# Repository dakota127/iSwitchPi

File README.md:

# iSwitchPi
Intelligent Power Switch for Raspberry Pi 

Native Raspberry Pi does not have an On/Off switch and there is no easy way
to shutdown the Pi while keeping the filesystem intact.
This Intelligent Power Switch allows just that: 
Power-On the Pi by pressing a pushbutton and also properly Power-Off
the Pi with another press on the same button.
The intelligence is provided by a program running in an AVR MCU ATtiny44.
This C-program implements a Finite State Machine in the MCU.
A small Python script is running in the Pi itself. 
Just one GPIO-Pin is used for two-way communication.
In addition, a variable frequency square wave is available for externally interrupting the Pi.

Formfactor: Raspi hat with 2x20 Pins for other hats on top of iSwitchPi.

Full Documentation, Code and EagleCAD files on GitHub. 
Documentation is in English and German.
Quick Start guide explains installation.  
See state diagram to understand operation of iSwitchPi

Also check out my project webpage at 
http://projects.descan.com/projekt5.html

Update April 2017:
In April of 2017 an update was made to the firmware in the ATtiny44. 
A user requested an auto-power-on functionality: the Pi should restart 
unattended (meaning without the need to press the ON-pushbutton) when 5 Volt comes back after a power failure. 
State 0 was added to the state diagram  and position 4 of dip-switch 3 is used to select/deselect this feature.

Free to use, modify, and distribute with proper attribution.
Frei für jedermann, vollständige Quellangabe vorausgesetzt.

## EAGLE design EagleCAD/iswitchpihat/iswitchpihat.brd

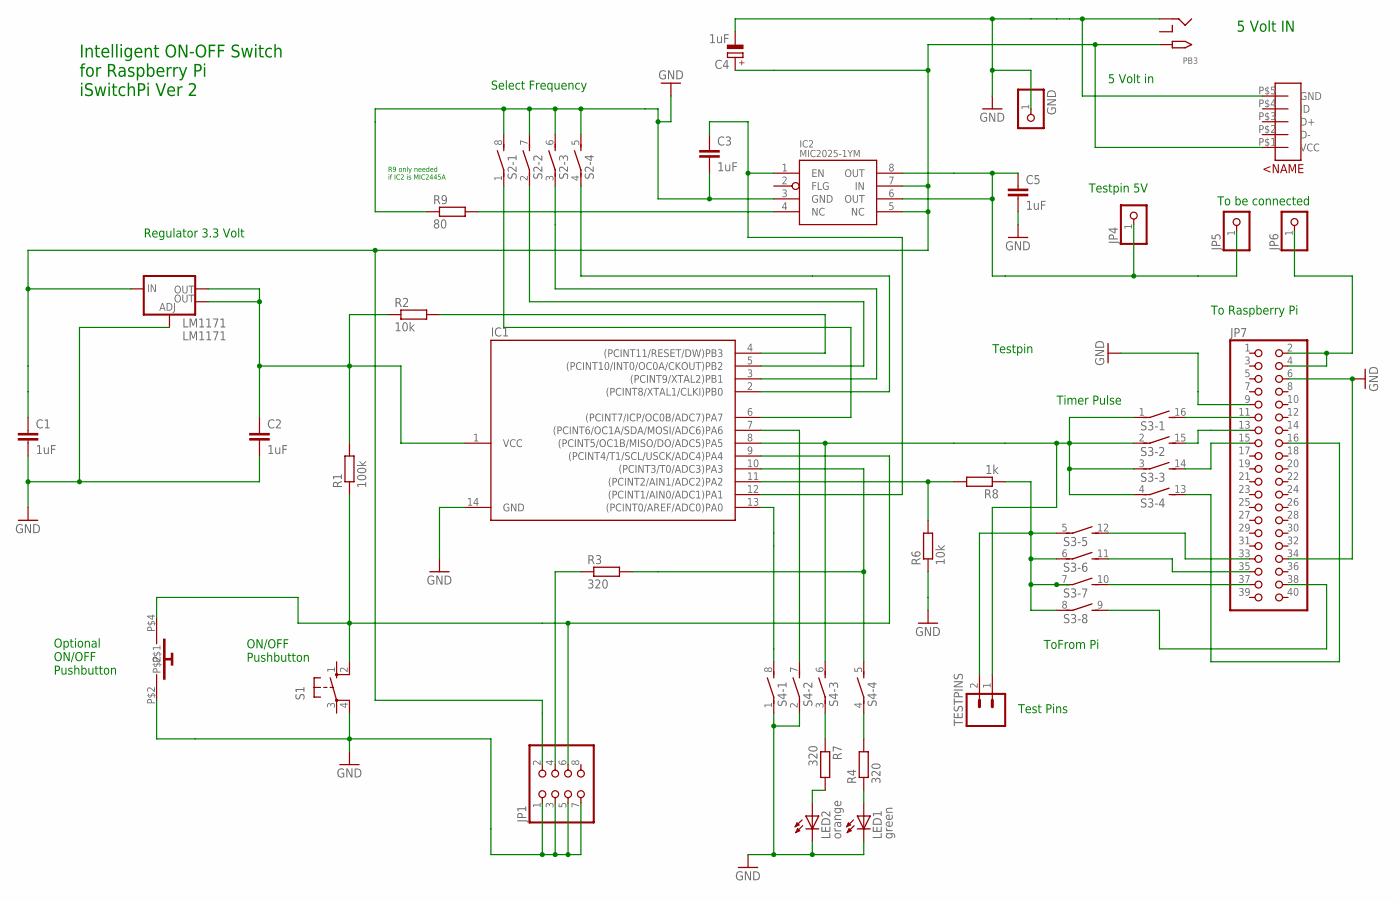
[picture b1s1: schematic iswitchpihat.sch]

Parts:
C1, C2, C3, C5: 1uF; C1206
C4: 1uF; E2,5-6E
GND: PINHD-1X1; 1X01
IC1: ATTINY24/44/84-PU; DIL14
IC2: MIC2025-1YM; SO08
JP1: PINHD-2X4; 2X04
JP4, JP5, JP6: PINHD-1X1; 1X01
JP7: PINHD-2X20-BIG; 2X20-BIG
LED1: green; 1206
LED2: orange; 1206
LM1171: LM1171; SOT223
PB1: PB6A-ELEDIS; PA52
PB3: 2.1MMJACK; ISWITCHPI_PJ-SMALLHOLES
PB4: USBMICRO; ADAUSBMICRO
R1: 100k; 0204/7
R2, R6: 10k; 0204/7
R3, R4, R7: 320; 0204/7
R8: 1k; 0204/7
R9: 80; 0204/7
S1: 10-XX; B3F-10XX
S2, S4: DIP04S
S3: DIP08S
TESTPINS: M02PTH; 1X02

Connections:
3.3V: C2.1, IC1.1 (VCC), LM1171.2 (OUT), LM1171.4 (OUT), R1.2, R2.1
5VIN: C1.1, C4.+, IC2.5 (NC), IC2.7 (IN), JP1.2, LM1171.3 (IN), PB3.TIP, PB4.P$1 (VCC)
5VOUT: C5.1, IC2.6 (OUT), IC2.8 (OUT), JP4.1, JP5.1
GND: C1.2, C2.2, C3.2, C4.-, C5.2, GND.1, IC1.14 (GND), IC2.3 (GND), JP1.1, JP1.3, JP1.5, JP1.7, JP7.6, JP7.9, JP7.34, LED1.C, LED2.C, LM1171.1 (ADJ), PB1.P$2, PB3.RING, PB4.P$5 (GND), R6.1, R9.1, S1.4 (P1), S2.5 (2), S2.6 (2), S2.7 (2), S2.8 (2), S4.1, S4.2 (1)
unnamed: IC1.9 ((PCINT4/T1/SCL/USCK/ADC4)PA4), JP1.6, PB1.P$4, R1.1, S1.2 (S1)
unnamed: IC1.6 ((PCINT7/ICP/OC0B/ADC7)PA7), S2.1
unnamed: JP7.11, S3.16 (2)
unnamed: IC1.4 ((PCINT11/RESET/DW)PB3), R2.2
unnamed: C3.1, IC1.12 ((PCINT1/AIN0/ADC1)PA1), IC2.1 (EN)
unnamed: IC1.11 ((PCINT2/AIN1/ADC2)PA2), R6.2, R8.2
unnamed: R8.1, S3.5 (1), S3.6 (1), S3.7 (1), S3.8 (1), TESTPINS.2
unnamed: IC1.10 ((PCINT3/T0/ADC3)PA3), R3.2, S4.5 (2)
unnamed: JP7.13, S3.15 (2)
unnamed: R7.1, S4.3 (1)
unnamed: LED1.A, R4.1
unnamed: JP1.4, R3.1
unnamed: LED2.A, R7.2
unnamed: JP7.15, S3.14 (2)
unnamed: JP7.16, S3.13 (2)
unnamed: R4.2, S4.4 (1)
unnamed: IC1.2 ((PCINT8/XTAL1/CLKI)PB0), S2.4 (1)
unnamed: JP7.38, S3.9 (2)
unnamed: IC1.5 ((PCINT10/INT0/OC0A/CKOUT)PB2), S2.2 (1)
unnamed: IC1.3 ((PCINT9/XTAL2)PB1), S2.3 (1)
unnamed: JP6.1, JP7.2, JP7.4
unnamed: JP7.37, S3.10 (2)
unnamed: JP7.35, S3.11 (2)
unnamed: JP7.33, S3.12 (2)
unnamed: IC1.7 ((PCINT6/OC1A/SDA/MOSI/ADC6)PA6), S4.7 (2)
unnamed: IC1.13 ((PCINT0/AREF/ADC0)PA0), S4.8 (2)
unnamed: IC1.8 ((PCINT5/OC1B/MISO/DO/ADC5)PA5), S3.1, S3.2 (1), S3.3 (1), S3.4 (1), S4.6 (2), TESTPINS.1
unnamed: IC2.4 (NC), R9.2

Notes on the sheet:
To Raspberry Pi
ON/OFF Pushbutton
Intelligent ON-OFF Switch for Raspberry Pi iSwitchPi Ver 2
5 Volt in
ToFrom Pi
Timer Pulse
Testpin
Testpin 5V
5 Volt IN
Optional ON/OFF Pushbutton
Regulator 3.3 Volt
Select Frequency
Test Pins
R9 only needed if IC2 is MIC2445A
To be connected

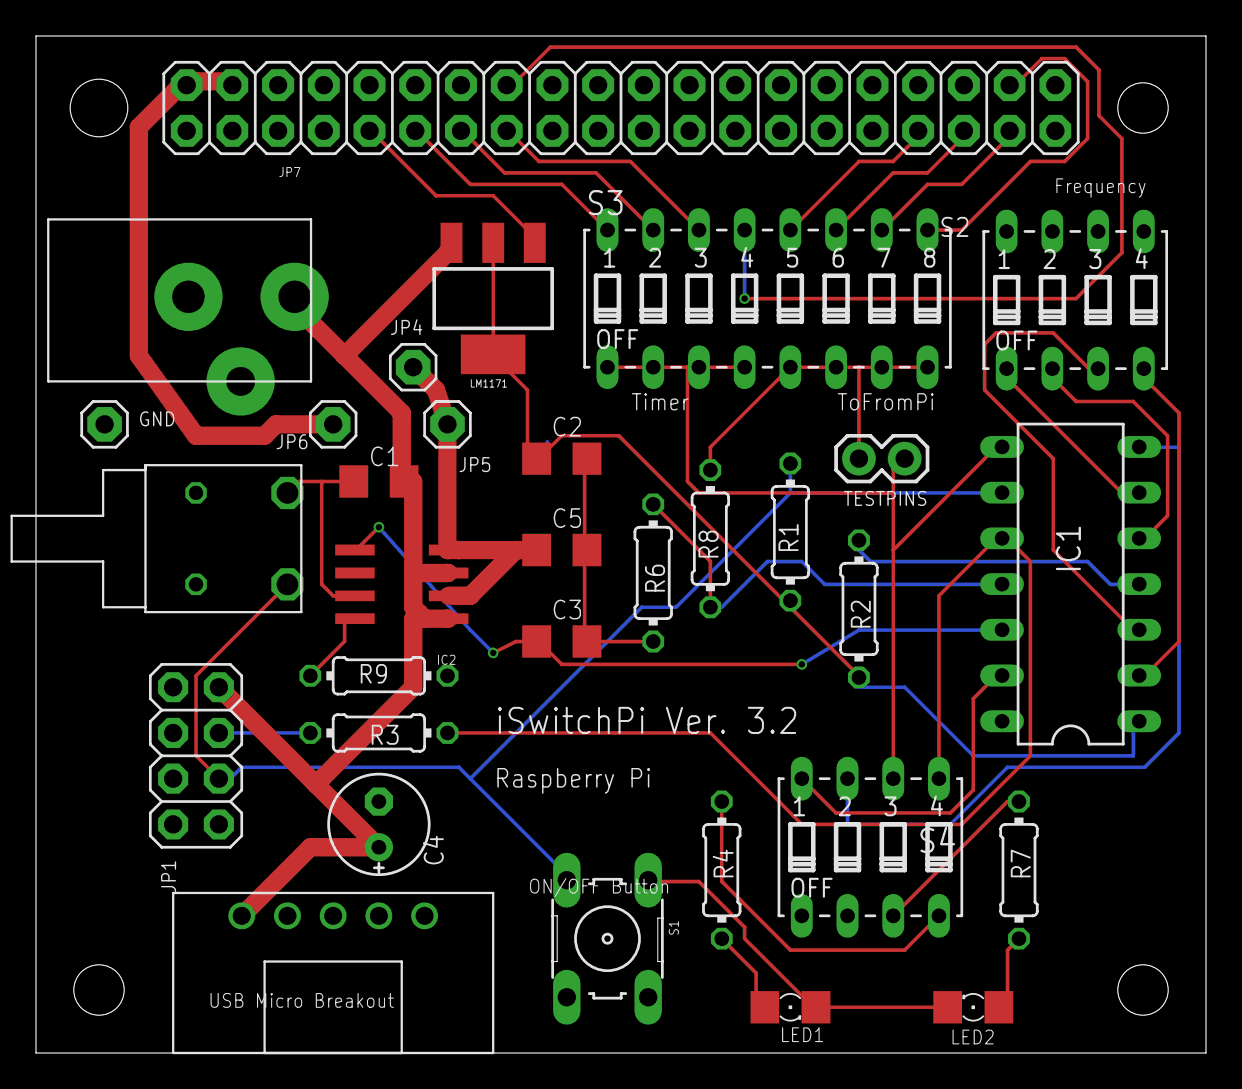
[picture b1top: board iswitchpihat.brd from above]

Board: 2 copper layers, 65.0 x 56.5 mm, 32 parts (0 on the bottom side), 32 nets.

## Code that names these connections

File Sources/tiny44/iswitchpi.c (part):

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/*		ATTiny44  Pin Usage						                        */
/*	   				         ----o----                                  */
/*       	     	    VCC|       |GND									*/
/*     DIP 1   	    PB0|       |PA0		TESTPIN						    */
/*     DIP 2       	PB1|       |PA1		5V on/off						*/
/*     Reset       	PB3|       |PA2		TofromPi					    */
/*     DIP 3       	PB2|       |PA3		Led								*/
/*     TESTPIN      PA7|       |PA4		Pushbutton					    */
/*     Delay       	PA6|       |PA5		Squarewave out                  */
/*                	  	--------     					    		     */
/*                                                                      */
/*	Uses Timer0 for debouncing pushbutton and Timer1 for generation     */
/*  of square wave on Pin PA5  (Fast PWM mode)   						*/
/*											                            */
/* 	Includes Debouncing 8 Keys with Repeat Function by Peter Dannegger  */
/* 	Found here:  http://www.mikrocontroller.net/topic/48465             */
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    TIMSK0 = 1<<OCIE0A;                             // Enable compare Match interrupt on Timer/Counter 0
                                                    // Achtung: TIMSK für tiny85 und TIMSK0 für tiny44

    pwm_init();                                     // setup Timer 1 for variable pulse on PA5 also set PORTB
    sei();                                          // Interrupt enable
    blinkwhat=0x00;                                 // do not blink
    first_time = 0xff;                                   //bits for first_time run thru the states
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            blinkwhat=PULSED_Blink;
            tick2=0;
            blinkon=1;
            pwm_stop();							// stop pulse genaration output on PA5
            pastpulses=0;                       // pulse counter reset (pulses from Pi)
            first_time =0xff;                   // set first_time all other states
            first_time &= ~(1<<STAT1_FIRST);    // clear first_time this state
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            PORTA |= (1<<VPOWER);               //switch 5 volt power on
            poweron_delay=POWERON_Delay_long;
            if ( !(PINA & (1<<DELAYTIME)) ) {
              poweron_delay=POWERON_Delay_short;            // check pin PA6 for delay times (Dip-switch 4 Pos 2 ON)
            }

            blinkwhat=REGULAR_Blink;
            blinkint=POWERON_Blink_int;
            tick2=0;                            //start timer
            sekunde=0;
            pwm_start();						            // start pulse generation output on PA5
            first_time =0xff;                   // set first_time all other states
            first_time &= ~( 1<<STAT2_FIRST);    // clear first_time this state
            }
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            first_time =0xff;                        // set first_time all other states
            first_time &= ~( 1<<STAT3_FIRST);        // clear first_time this state
            }
        pwm_check();						// check various inputs for frequency of pulse on PA5

        if  (get_key_short( 1<<KEY0 )) {         // get debounced keypress short
            cli();
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            state=state5;                          // next state 5
            poweroff_delay=POWEROFF_Delay_HALT_long;  // Poweroff delay for halt
            if ( !(PINA & (1<<DELAYTIME)) ) {
              poweroff_delay=POWEROFF_Delay_HALT_short;        // check pin PA6 for delay times (Dip-switch 4 Pos 2 ON)
              }

            }
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                                                    // Pi will reboot
            poweroff_delay=POWEROFF_Delay_REBOOT_long;  // Poweroff delay for halt
            if ( !(PINA & (1<<DELAYTIME)) ) {
              poweroff_delay=POWEROFF_Delay_REBOOT_short;   // check pin PA6 for delay times (Dip-switch 4 Pos 2 ON)
              }

        }
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
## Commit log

2016-12-07 docu updated
2016-12-08 Readme updated
2016-12-11 board updated, partslist added
2016-12-12 partslist updated
2016-12-16 debug prints enhanced
2016-12-16 components diagram added
2016-12-17 description updated
2016-12-18 eagle files added
2016-12-18 optparse replaced with argparse
2016-12-19 start pulse generator modified
2016-12-19 Project Descr. english added
2016-12-19 Project Descr. German updated
2016-12-20 Python script and Makefile updated
2016-12-20 Duco updated
2016-12-21 folder docu reorganized
2016-12-21 english descr.updated
2016-12-21 picture folder added
2017-01-02 pcb board updated:dip switch moved
2017-01-04 small changes
2017-01-05 New Version with DemoMode
2017-01-05 new state diagram
2017-01-05 update state diagram
2017-01-06 state diagram english added
2017-01-06 state diagram layers removed
2017-01-06 many thing updated for new board
2017-01-08 example scripts added, docu updated
2017-01-08 old docu removed
2017-01-08 new board documented
2017-01-09 iswitchpi.c modified, docu modified
2017-01-09 english docu modified
2017-01-09 delaytimes adjusted
2017-01-17 quickstart updated
2017-01-21 docu updated - new board
2017-01-23 square.c comments added
2017-01-23 new pictures
2017-01-26 german docu updated
2017-03-12 Quickstart Guide updated
2017-04-27 Auto-power-on added
2017-04-27 Docu updates
2021-08-04 print statements modified for python3

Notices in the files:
parts and their libraries:
SparkFun-PowerIC: Licensing: Creative Commons ShareAlike 4.0 International - https://creativecommons.org/licenses/by-sa/4.0
